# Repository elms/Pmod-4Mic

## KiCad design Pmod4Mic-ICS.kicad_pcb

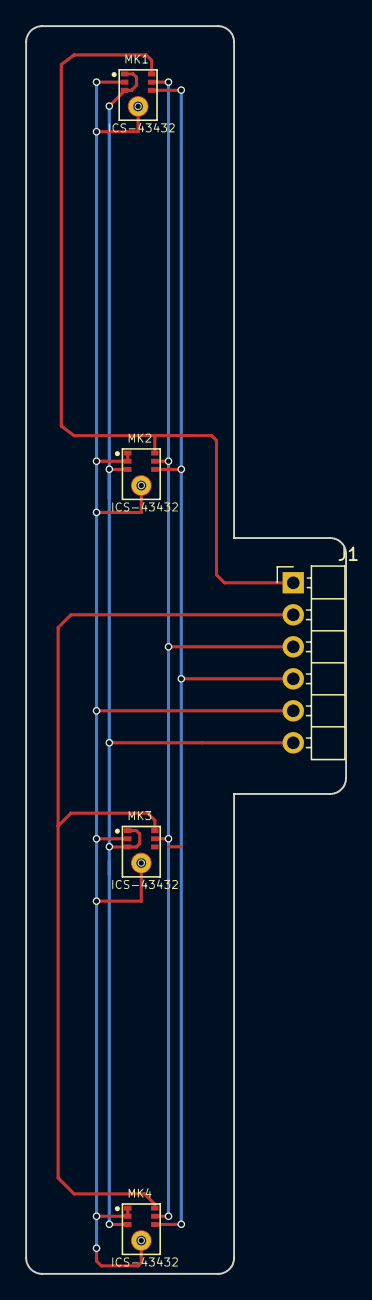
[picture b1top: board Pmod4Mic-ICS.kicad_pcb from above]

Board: 2 copper layers, 25.4 x 99.1 mm, 5 parts (0 on the bottom side), 6 nets.

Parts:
J1: CONN_01X06; Pin_Header_Angled_1x06_Pitch2.54mm
MK1, MK2, MK3, MK4: ICS-43432; MIC_ICS-43432

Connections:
/D0: J1.2, MK3.7, MK4.7
/D1: J1.1, MK1.7, MK2.7
/GND: J1.5, MK1.2, MK1.4, MK2.1, MK2.2, MK2.4, MK3.2, MK3.4, MK4.1, MK4.2, MK4.4
/SCLK: J1.3, MK1.6, MK2.6, MK3.6, MK4.6
/VDD: J1.6, MK1.1, MK1.3, MK2.3, MK3.1, MK3.3, MK4.3
/WS/WCLK: J1.4, MK1.5, MK2.5, MK3.5, MK4.5

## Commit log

2018-05-09 v0.1 with ICS
2018-05-09 Added line labels and fixed errors
2018-05-09 Adding test points, caps, and Resistors with passing ERC/DRC
